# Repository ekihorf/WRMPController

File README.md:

# WMRPController

DIY soldering iron controller for Weller RT tips.

There are many projects of controllers for Weller tips, but most use a DC power supply and PWM power control. This one uses AC power for the heating element. The power is controlled using zero-crossing switching, so EMI is reduced to a minimum.

I used a 3D printed handle for the RT tips, which can be found here: http://kair.us/projects/weller/diy_wmrp_handle/index.html.

This project is a playground for learning C++ on microcontrollers, so don't expect perfectly clean code ;).

### What is already implemented and works well
- AC control using triac with zero-crossing switching
- PID temperature controller
- User interface
- Storing settings in EEPROM
- Storing the last set temperature in EEPROM (uses wear levelling)
- Standby and auto power off

### What needs to be improved
- Temperature measurement. There is a small glitch (drop) in temperature every ~15 seconds

### What is NOT going to be implemented
- Cold junction compensation of the thermocouple. This device is for hobby use only and small difference in the tip temperature is not really a problem. Adding this feature would require additional wire and a temperature sensor, which would make the cable for the handle less flexible.

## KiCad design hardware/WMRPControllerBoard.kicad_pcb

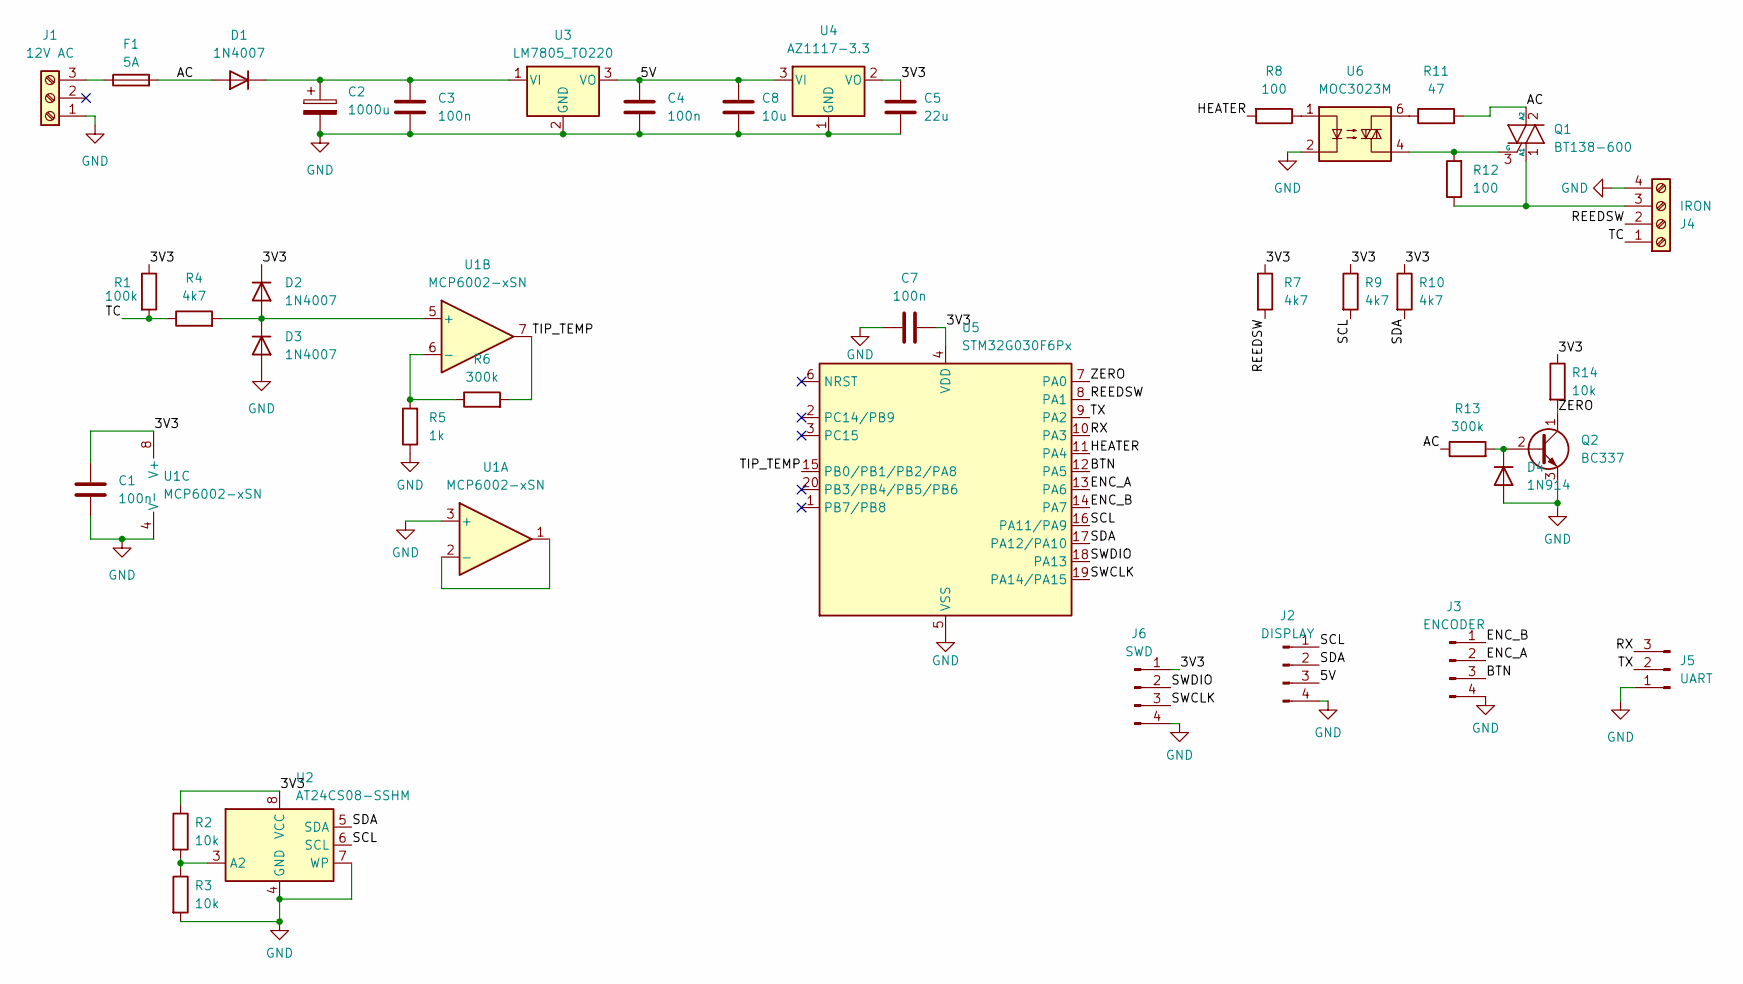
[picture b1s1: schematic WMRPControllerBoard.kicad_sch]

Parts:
C1, C3, C4, C7: 100n; C_0805_2012Metric_Pad1.18x1.45mm_HandSolder
C2: 1000u; CP_Radial_D13.0mm_P5.00mm
C5: 22u; C_1206_3216Metric_Pad1.33x1.80mm_HandSolder
C8: 10u; C_1206_3216Metric_Pad1.33x1.80mm_HandSolder
D1, D2, D3: 1N4007; D_DO-41_SOD81_P10.16mm_Horizontal
D4: 1N914; D_DO-35_SOD27_P7.62mm_Horizontal
F1: 5A; Fuseholder_Clip-5x20mm_Littelfuse_111_Inline_P20.00x5.00mm_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
J1: 12V AC; TerminalBlock_RND_205-00013_1x03_P5.00mm_Horizontal
J2: DISPLAY; PinHeader_1x04_P2.54mm_Vertical
J3: ENCODER; PinHeader_1x04_P2.54mm_Vertical
J4: IRON; TerminalBlock_RND_205-00014_1x04_P5.00mm_Horizontal
J5: UART; PinHeader_1x03_P2.54mm_Vertical
J6: SWD; PinHeader_1x04_P2.54mm_Vertical
Q1: BT138-600; TO-220-3_Vertical
Q2: BC337; TO-92_Inline_Wide
R1: 100k; R_0805_2012Metric_Pad1.20x1.40mm_HandSolder
R2, R3: 10k; R_0805_2012Metric_Pad1.20x1.40mm_HandSolder
R4, R7, R9, R10: 4k7; R_Axial_DIN0207_L6.3mm_D2.5mm_P7.62mm_Horizontal
R5: 1k; R_0805_2012Metric_Pad1.20x1.40mm_HandSolder
R6, R13: 300k; R_0805_2012Metric_Pad1.20x1.40mm_HandSolder
R8: 100; R_Axial_DIN0207_L6.3mm_D2.5mm_P7.62mm_Horizontal
R11: 47; R_0805_2012Metric_Pad1.20x1.40mm_HandSolder
R12: 100; R_0805_2012Metric_Pad1.20x1.40mm_HandSolder
R14: 10k; R_Axial_DIN0207_L6.3mm_D2.5mm_P7.62mm_Horizontal
U1: MCP6002-xSN; SOIC-8_3.9x4.9mm_P1.27mm
U2: AT24CS08-SSHM; SOIC-8_3.9x4.9mm_P1.27mm
U3: LM7805_TO220; TO-220-3_Vertical
U4: AZ1117-3.3; SOT-89-3_Handsoldering
U5: STM32G030F6Px; TSSOP-20_4.4x6.5mm_P0.65mm
U6: MOC3023M; SMDIP-6_W9.53mm

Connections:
/3V3: C1.1, C5.1, C7.2, D2.1 (K), J6.1, R1.1, R2.1, R7.1, R9.1, R10.1, R14.1, U1.8 (V+), U2.8 (VCC), U4.2 (VO), U5.4 (VDD)
/5V: C4.1, C8.1, J2.3, U3.3 (VO), U4.3 (VI)
/AC: D1.2 (A), F1.2, Q1.2 (A2), R11.2, R13.1
/BTN: J3.3, U5.12 (PA5)
/ENC_A: J3.2, U5.13 (PA6)
/ENC_B: J3.1, U5.14 (PA7)
/HEATER: R8.2, U5.11 (PA4)
/REEDSW: J4.2, R7.2, U5.8 (PA1)
/RX: J5.3, U5.10 (PA3)
/SCL: J2.1, R9.2, U2.6 (SCL), U5.16 (PA11/PA9)
/SDA: J2.2, R10.2, U2.5 (SDA), U5.17 (PA12/PA10)
/SWCLK: J6.3, U5.19 (PA14/PA15)
/SWDIO: J6.2, U5.18 (PA13)
/TC: J4.1, R1.2, R4.1
/TIP_TEMP: R6.2, U1.7, U5.15 (PB0/PB1/PB2/PA8)
/TX: J5.2, U5.9 (PA2)
/ZERO: Q2.1 (C), R14.2, U5.7 (PA0)
GND: C1.2, C2.2, C3.2, C4.2, C5.2, C7.1, C8.2, D3.2 (A), D4.2 (A), J1.1, J2.4, J3.4, J4.4, J5.1, J6.4, Q2.3 (E), R3.2, R5.1, U1.3 (+), U1.4 (V-), U2.4 (GND), U2.7 (WP), U3.2 (GND), U4.1 (GND), U5.5 (VSS), U6.2
unnamed: C2.1, C3.1, D1.1 (K), U3.1 (VI)
unnamed: D2.2 (A), D3.1 (K), R4.2, U1.5 (+)
unnamed: D4.1 (K), Q2.2 (B), R13.2
unnamed: F1.1, J1.3
unnamed: J4.3, Q1.1 (A1), R12.1
unnamed: Q1.3 (G), R12.2, U6.4
unnamed: R8.1, U6.1
unnamed: R11.1, U6.6
unnamed: U1.1, U1.2 (-)
unnamed: R5.2, R6.1, U1.6 (-)
unnamed: R2.2, R3.1, U2.3 (A2)

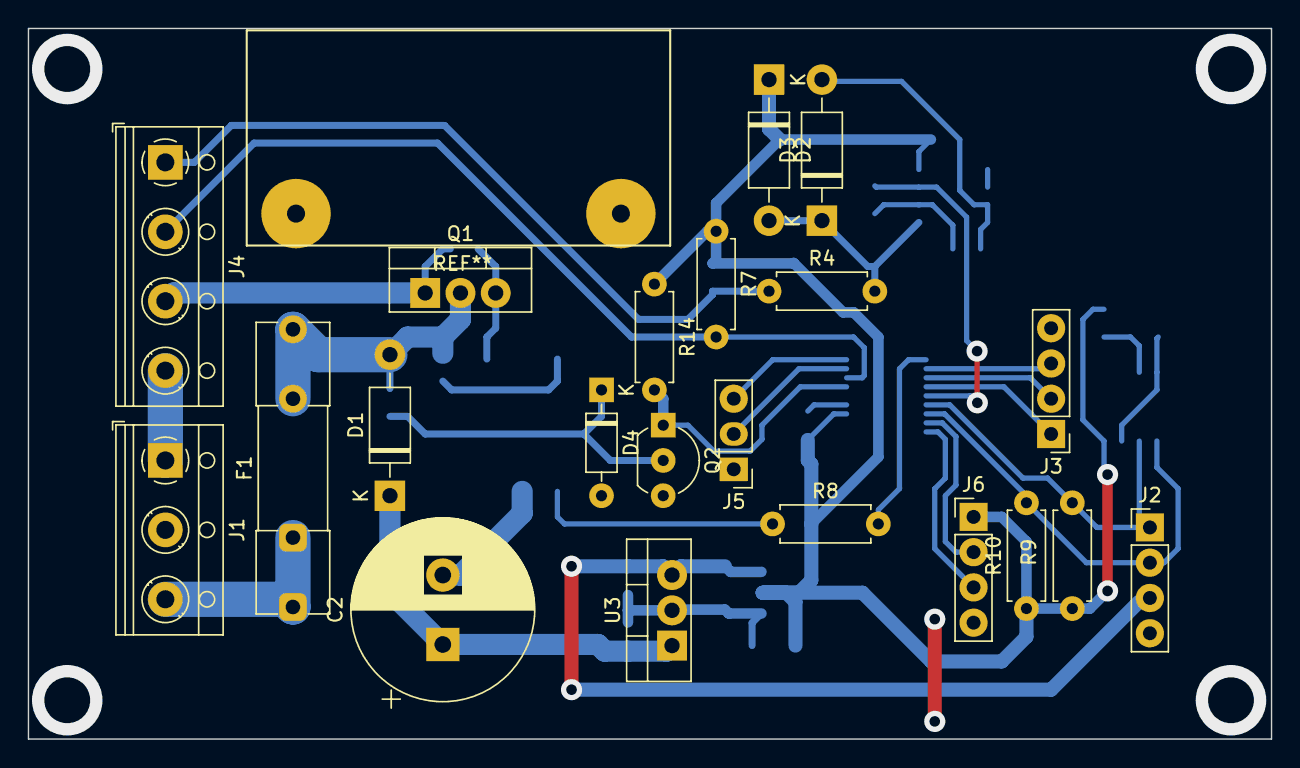
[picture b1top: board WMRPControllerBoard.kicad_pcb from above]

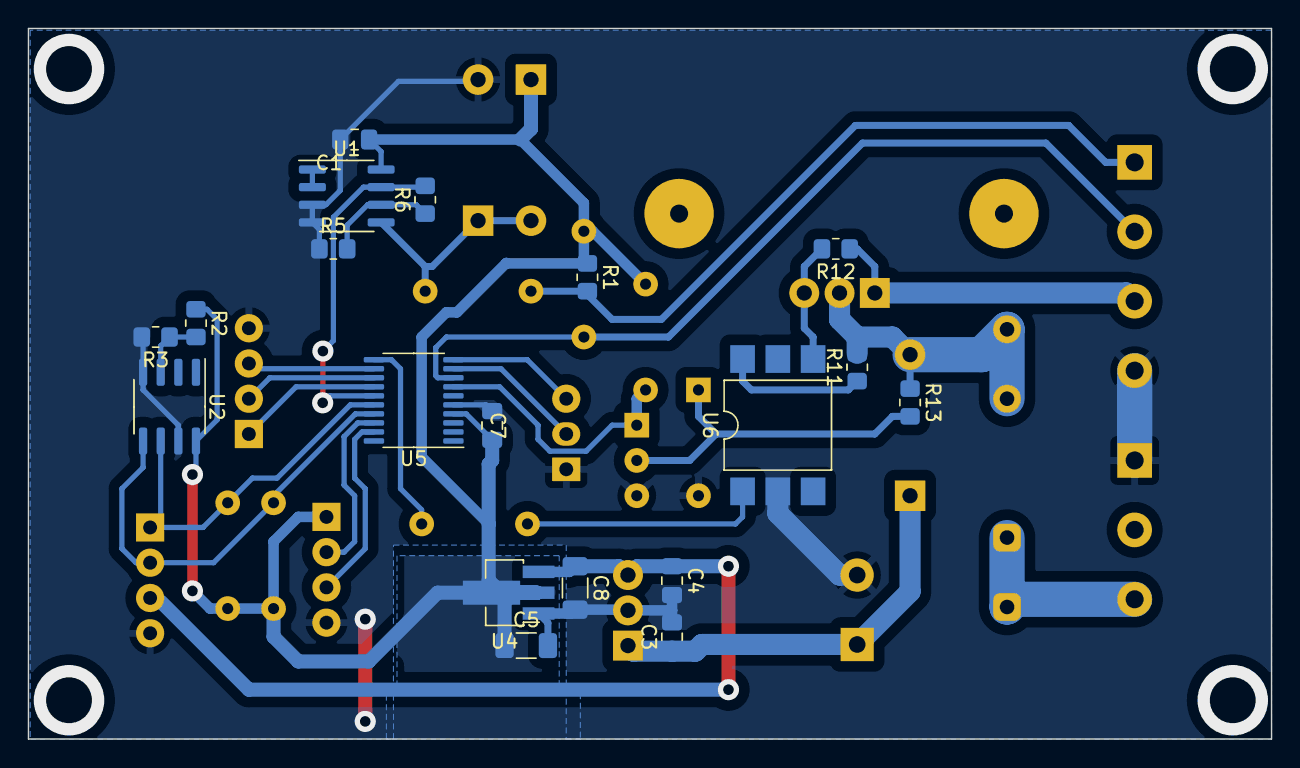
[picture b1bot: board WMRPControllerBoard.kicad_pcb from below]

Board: 2 copper layers, 89.5 x 51.2 mm, 40 parts (19 on the bottom side), 29 nets.

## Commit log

2023-11-20 Implement encoder handling
2023-11-20 Implement display driver
2023-11-20 Add printN method to display driver
2023-11-20 Implement UI views
2023-11-20 Use DMA for I2C comm
2023-11-20 Change AcControl algorithm
2023-11-20 Add debug task
2023-11-20 Add ADC reading
2023-11-20 Refactor TempSensor
2023-11-20 Implement debugging interface
2023-11-20 Implement main view
2023-11-20 Use 64-bit tick counter
2023-11-20 Add temperature conversion (type D thermocouple)
2023-11-20 Add button library
2023-11-20 Fix bug in SysTick
2023-11-20 Refactor Debug module and main logic
2023-11-20 Move unit definitions to separate file
2023-11-20 Implement abstraction layer for interrupt handlers
2023-11-20 Refactor Time module
2023-11-20 Implement PID controller
2023-11-20 Refactor delay class
2023-11-20 Implement task scheduler
2023-11-20 Enable watchdog
2023-11-20 Select correct DMAREQ_ID for given I2C periph
2023-11-20 Implement saving settings to EEPROM
2023-11-20 Implement display of fixed point numbers
2023-11-20 Move configs to BoardConfig.h
2023-11-20 Get rid of warnings
2023-11-20 Change tc amp gain
2023-11-20 Fix pid controller
2023-11-20 Implement settings view
2023-11-20 Check if set temp in eeprom is valid
2023-11-20 Add schematics and PCB
2023-11-20 Refactor driver configurations
2023-11-20 Change Pid interface
2023-11-20 Implement standby and auto off
2023-11-20 Add entries to settings menu
2023-11-20 Reset watchdog from control task
2023-11-20 Implement reading from EEPROM
2023-11-20 Implement signed integer to string conversion
2023-11-20 Refactor Units
2023-11-20 Refactor main logic
2023-11-20 Refactor driver interfaces
2023-11-20 Add handling of fixed point parameters
2023-11-20 Add README
2023-11-20 Add custom display symbols
2023-11-20 Change pid defaults
2023-11-20 Change debug format
2023-11-20 Remove commented out code
2023-11-20 Redesign UI
2023-11-20 Implement Short Term Storage
2023-11-20 Implement Long Term Storage
2023-11-20 Use error instead of input in PID derivative calculation
2023-11-20 Update menu parameters
2023-11-20 Reenable watchdog
2023-11-20 Update default settings
2023-11-23 Fix minor UI bug
